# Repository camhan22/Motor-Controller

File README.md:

# Motor-Controller

12-48VDC 65A continuous (150A Peak) 0-100% duty cycle brushed DC motor driver 

Communicates to a master controller through I2C with commands that look like the following:

DSSSSSSS

Where D is the direction (0 or 1) (1 will apply +VDC to Motor+ Terminal) (0 Will apply +VDC to the Motor- Terminal)
S is the duty cycle from 0-100% (This is checked by the software to ensure it is within bounds) (Anything out of bounds is clamped to 100%)

I2C address can be changed with the dip switches on the board and allows up to 8 motor drivers to run at the same time.

Returns a status byte to describe what the controller is doing. If faults are present, there are seperate status codes for each failure and can be found within the code folder in the controller status codes excel sheet.

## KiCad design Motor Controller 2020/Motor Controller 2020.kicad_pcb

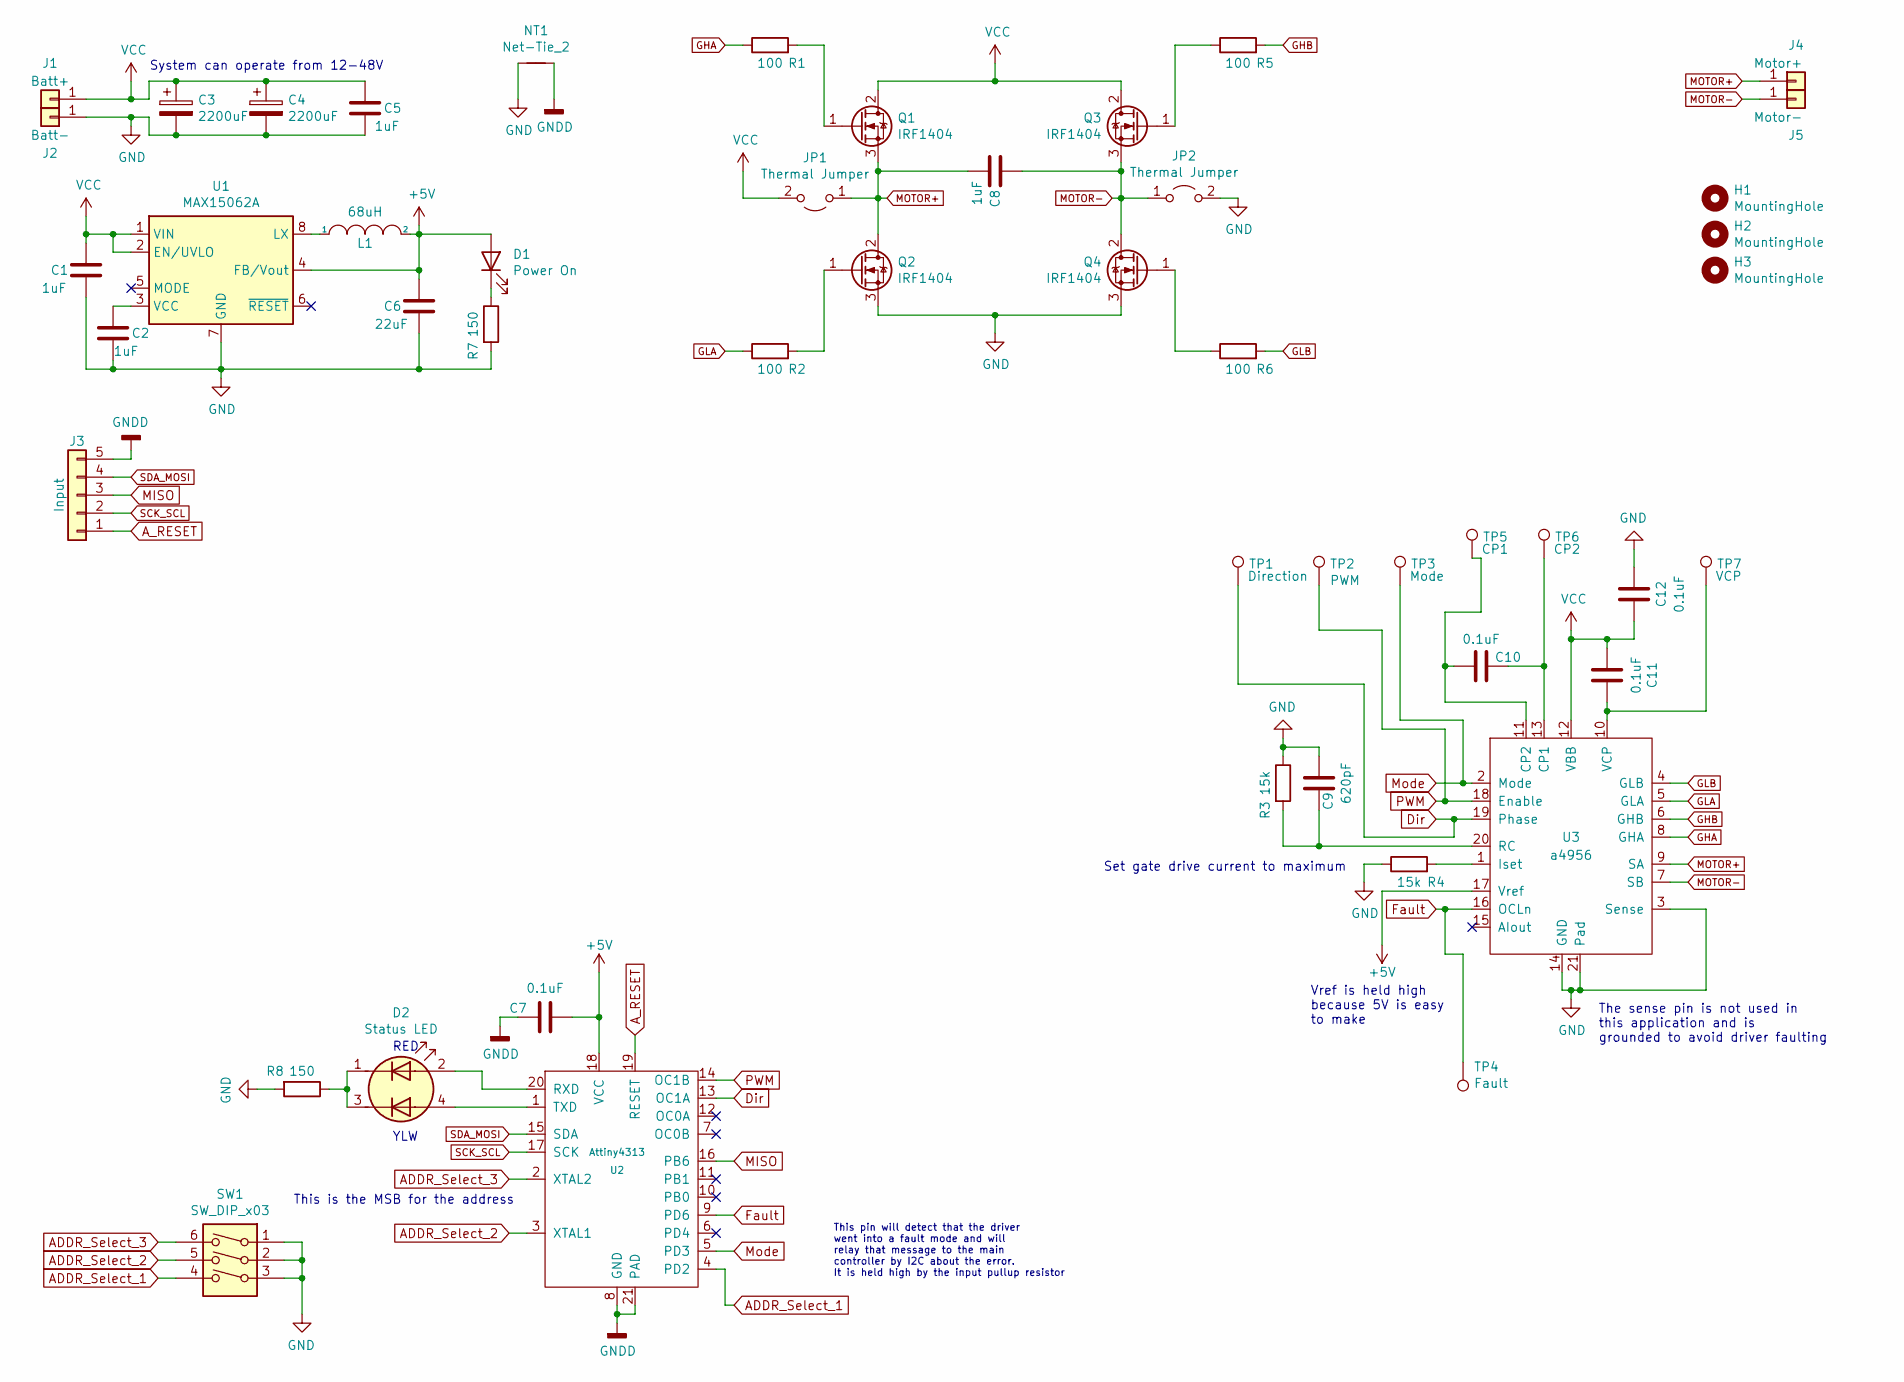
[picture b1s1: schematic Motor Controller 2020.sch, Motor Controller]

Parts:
C1, C2, C5: 1uF; C_1210_3225Metric
C3, C4: 2200uF; C_Radial_D18.0mm_H35.5mm_P7.50mm
C6: 22uF; C_1210_3225Metric
C7, C10, C11, C12: 0.1uF; C_1812_4532Metric_Pad1.57x3.40mm_HandSolder
C8: 1uF; C_Disc_D5.0mm_W2.5mm_P2.50mm
C9: 620pF; C_1210_3225Metric
D1: Power On; LED_1206_3216Metric
D2: Status LED; LED_0603_4_pin
H1, H2, H3: MountingHole; MountingHole_3.2mm_M3
J1: Batt+; Wuerth_REDCUBE-THR_WP-THRBU_74650195_THR
J2: Batt-; Wuerth_REDCUBE-THR_WP-THRBU_74650195_THR
J3: Input; Molex_KK-254_AE-6410-05A_1x05_P2.54mm_Vertical
J4: Motor+; Wuerth_REDCUBE-THR_WP-THRBU_74650195_THR
J5: Motor-; Wuerth_REDCUBE-THR_WP-THRBU_74650195_THR
JP1, JP2: Thermal Jumper; R_2512_6332Metric
L1: 68uH; L_1210_3225Metric
NT1: Net-Tie_2; NetTie-2_SMD_Pad2.0mm
Q1, Q2, Q3, Q4: IRF1404; TO-263-2
R1, R2, R5, R6: 100; R_2010_5025Metric
R3, R4: 15k; R_2010_5025Metric_Pad1.40x2.65mm_HandSolder
R7, R8: 150; R_1206_3216Metric
SW1: SW_DIP_x03; SW_DIP_SPSTx03_Slide_6.7x9.18mm_W8.61mm_P2.54mm_LowProfile
TP1: Direction; TestPoint_Pad_D1.0mm
TP2: PWM; TestPoint_Pad_D1.0mm
TP3: Mode; TestPoint_Pad_D1.0mm
TP4: Fault; TestPoint_Pad_D1.0mm
TP5: CP1; TestPoint_Pad_D1.0mm
TP6: CP2; TestPoint_Pad_D1.0mm
TP7: VCP; TestPoint_Pad_D1.0mm
U1: MAX15062A; DFN-8_2x2mm_P0.5mm
U2: Attiny4313; VQFN-20-1EP_3x3mm_P0.4mm_EP1.7x1.7mm_ThermalVias
U3: a4956; MLF-20-1EP_4x4mm_P0.5mm_EP2.6x2.6mm_ThermalVias

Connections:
+5V: C6.1, C7.2, D1.2 (A), L1.2, U1.4 (FB/Vout), U2.18 (VCC), U3.17 (Vref)
ADDR_Select_1: SW1.4, U2.4 (PD2)
ADDR_Select_2: SW1.5, U2.3 (XTAL1)
ADDR_Select_3: SW1.6, U2.2 (XTAL2)
A_RESET: J3.1, U2.19 (RESET)
Dir: TP1.1, U2.13 (OC1A), U3.19 (Phase)
Fault: TP4.1, U2.9 (PD6), U3.16 (OCLn)
GHA: R1.1, U3.8 (GHA)
GHB: R5.2, U3.6 (GHB)
GLA: R2.1, U3.5 (GLA)
GLB: R6.2, U3.4 (GLB)
GND: C1.2, C2.2, C3.2, C4.2, C5.2, C6.2, C9.2, C12.1, J2.1, JP2.2 (B), NT1.1, Q2.3 (S), Q4.3 (S), R3.1, R4.1, R7.2, R8.2, SW1.1, SW1.2, SW1.3, U1.7 (GND), U3.3 (Sense), U3.14 (GND), U3.21 (Pad)
GNDD: C7.1, J3.5, NT1.2, U2.8 (GND), U2.21 (PAD)
MISO: J3.3, U2.16 (PB6)
MOTOR+: C8.2, J4.1, JP1.1 (A), Q1.3 (S), Q2.2 (D), U3.9 (SA)
MOTOR-: C8.1, J5.1, JP2.1 (A), Q3.3 (S), Q4.2 (D), U3.7 (SB)
Mode: TP3.1, U2.5 (PD3), U3.2 (Mode)
unnamed: C2.1, U1.3 (VCC)
unnamed: C9.1, R3.2, U3.20 (RC)
unnamed: C10.1, TP6.1, U3.13 (CP1)
unnamed: C10.2, TP5.1, U3.11 (CP2)
unnamed: C11.2, TP7.1, U3.10 (VCP)
unnamed: D1.1 (K), R7.1
unnamed: D2.1 (A1), D2.3 (A2), R8.1
unnamed: D2.2 (K1), U2.20 (RXD)
unnamed: D2.4 (K2), U2.1 (TXD)
unnamed: L1.1, U1.8 (LX)
unnamed: Q1.1 (G), R1.2
unnamed: Q2.1 (G), R2.2
unnamed: Q3.1 (G), R5.1
unnamed: Q4.1 (G), R6.1
unnamed: R4.2, U3.1 (Iset)
PWM: TP2.1, U2.14 (OC1B), U3.18 (Enable)
SCK_SCL: J3.2, U2.17 (SCK)
SDA_MOSI: J3.4, U2.15 (SDA)
VCC: C1.1, C3.1, C4.1, C5.1, C11.1, C12.2, J1.1, JP1.2 (B), Q1.2 (D), Q3.2 (D), U1.1 (VIN), U1.2 (EN/UVLO), U3.12 (VBB)

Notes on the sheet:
This pin will detect that the driver went into a fault mode and will relay that message to the main controller by I2C about the error. It is held high by the input pullup resistor
This is the MSB for the address
The sense pin is not used in this application and is grounded to avoid driver faulting
Vref is held high because 5V is easy to make
Set gate drive current to maximum
System can operate from 12-48V
YLW
RED

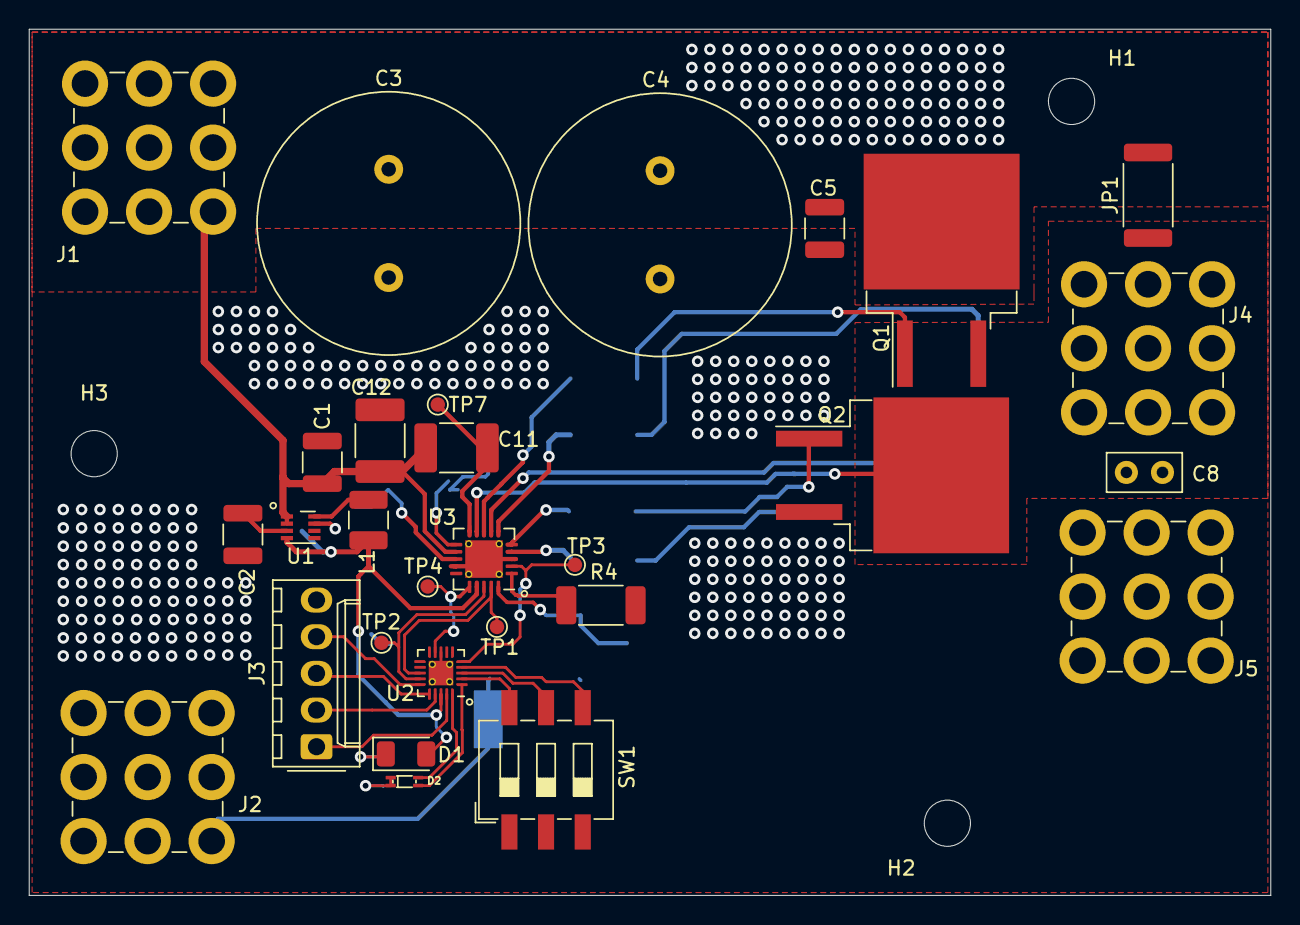
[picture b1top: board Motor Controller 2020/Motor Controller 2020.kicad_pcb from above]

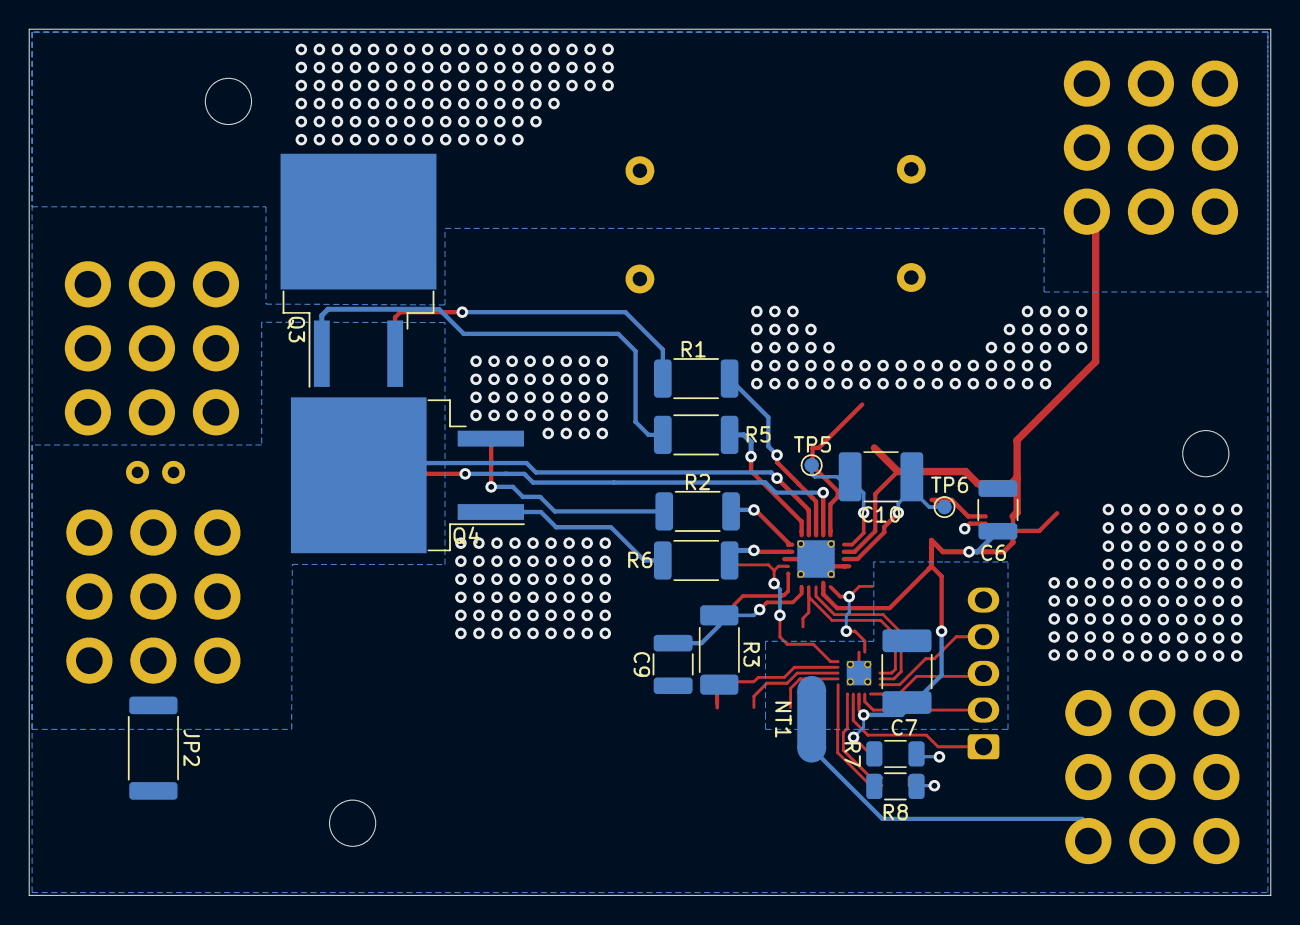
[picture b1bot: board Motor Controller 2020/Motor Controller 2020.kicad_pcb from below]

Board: 2 copper layers, 86.0 x 60.0 mm, 49 parts (17 on the bottom side), 36 nets.

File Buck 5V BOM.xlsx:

Schematic Annotation | Part Number | Description | Qty | Price | Supplier | Total Cost | Link
C7,C10,C11,C12 | 399-17501-1-ND | ±5% 50V Ceramic Capacitor X7R 1812 (4532 Metric) 0.1uF | 4 | 1.0900000000000001 | Digikey | 4.3600000000000003 | https://www.digikey.com/en/products/detail/kemet/C1812C104J5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
C8 | 445-173162-1-ND | 1 µF ±10% 100V Ceramic Capacitor X7R Radial | 1 | 0.73 | Digikey | 0.73 | https://www.digikey.com/en/products/detail/tdk-corporation/F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
C3,C4 | 1189-1505-ND | 2200 µF 63 V Aluminum Electrolytic Capacitors Radial, Can - 10000 Hrs @ 105°C | 2 | 2.92 | Digikey | 5.84 | https://www.digikey.com/en/products/detail/rubycon/63ZLH2200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
C9 | 478-10901-1-ND | CAP CER 620PF 100V NP0 1210 | 1 | 0.49 | Digikey | 0.49 | https://www.digikey.com/en/products/detail/avx-corporation/1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
R3,R4 | 541-15.0KACCT-ND | 15 kOhms ±1% 0.75W, 3/4W Chip Resistor 2010 (5025 Metric) Automotive AEC-Q200 T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 | 2 | 0.3 | Digikey | 0.6 | https://www.digikey.com/en/products/detail/vishay-dale/CRCW2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
D1 | 1080-1419-1-ND | Green 570nm LED Indication - Discrete 2.1V 1206 (3216 Metric) | 1 | 0.37 | Digikey | 0.37 | https://www.digikey.com/en/products/detail/QTLP650D4TR/1080-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
D2 | 1516-QBLP601-RYCT-ND | Red, Yellow 630nm Red, 591nm Yellow LED Indication - Discrete 2V Red, 2V Yellow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 | 1 | 0.43 | Digikey | 0.43 | https://www.digikey.com/en/products/detail/qt-brightek-qtb/Q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
R7,R8 | 311-150LJCT-ND | 150 Ohms ±1% 0.25W, 1/4W Chip Resistor 1206 (3216 Metric) Automotive AEC-Q200, 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 | 2 | 0.1 | Digikey | 0.2 | https://www.digikey.com/en/products/detail/AC1206FR-07150RL/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
Q1-Q4 | IRFS3306TRLPBFCT-ND | N-Channel 60 V 120A (Tc) 230W (Tc) Surface Mount D2PAK | 4 | 2.58 | Digikey | 10.32 | https://www.infineon.com/dgdl/irfs3306pbf.pdf?fileId=5546d46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
U3 | 620-1772-1-ND | Motor Driver NMOS Parallel | 1 | 1.64 | Digikey | 1.64 | https://www.digikey.com/en/products/detail/allegro-microsyst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
U1 | 175-MAX17640BATA+-ND | Buck Switching Regulator IC Positive Fixed 5V 1 Output 400mA 8-WFDFN | 1 | 1.65 | Digikey | 1.65 | https://www.digikey.com/en/products/detail/maxim-integrated/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
L1 | 587-3070-1-ND | 68 µH Unshielded Wirewound Inductor 410 mA 1.3Ohm Max 1210 (3225 Metric) | 1 | 0.3 | Digikey | 0.3 | https://www.digikey.com/en/products/detail/CBC3225T680KR/587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
C6 | 1276-CL32B226MOJVPNECT-ND | 22 µF ±20% 16V Ceramic Capacitor X7R 1210 (3225 Metric) | 1 | 0.71 | Digikey | 0.71 | CL32B226MOJVPNE Samsung Electro-Mechanics | Capacitors | DigiKey
C1,C2,C5 | 2873-C1210X105K101TCT-ND | 1 µF ±10% 100V Ceramic Capacitor X7R 1210 (3225 Metric) | 4 | 0.35 | Digikey | 1.4 | https://www.digikey.com/en/products/detail/holy-stone-enterp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
J1,J2,J4,J5 | 732-10888-1-ND | Pin Screw Terminal, Power Tap M5 Through Hole | 4 | 4.59 | Digikey | 18.36 | https://www.digikey.com/en/products/detail/w%C3%BCrth-elektr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
J3 | 23-0022292051-ND | Connector Header Through Hole 5 position 0.100" (2.54mm) | 1 | 1.43 | Digikey | 1.43 | https://www.digikey.com/en/products/detail/molex/0022292051/1130591
J3 Conn | 23-0010112053-ND | 5 Rectangular Connectors - Housings Receptacle White 0.100" (2.54mm) | 1 | 0.28999999999999998 | Digikey | 0.28999999999999998 | https://www.digikey.com/en/products/detail/molex/0010112053/171981
J3 Crimp | WM23941CT-ND | Non-Gendered Contact Gold 24-30 AWG Crimp - | 9 | 0.39 | Digikey | 3.5100000000000002 | https://www.digikey.com/en/products/detail/molex/0008550124/1784904
SW1 | 2223-DS04-254-2-03BK-SMT-ND | Dip Switch SPST Position Surface Mount Slide (Standard) Actuator 25mA 24VDC | 1 | 0.54 | Digikey | 0.54 | https://www.digikey.com/en/products/detail/cui-devices/DS04-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
JP1,JP2 | 764-THJP2512AST1CT-ND | Thermal Interface Products Therm Jumper 30 mil 2512 | 2 | 1.35 | Digikey | 2.7 | https://www.digikey.com/en/products/detail/vishay-dale-thin-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
 | 277-11158-ND | Ring Terminal Connector M5 Stud Circular 10-14 AWG Crimp | 4 | 0.26 | Digikey | 1.04 | https://www.digikey.com/en/products/detail/phoenix-contact/3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
R1,R2,R5,R6 | RMCP2010JT100RCT-ND | 100 Ohms ±5% 1W Chip Resistor 2010 (5025 Metric) Automotive AEC-Q200 Thick Film | 4 | 0.41 | Digikey | 1.64 | https://www.digikey.com/en/products/detail/stackpole-electro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
U2 | ATTINY4313-MMHRCT-ND | 8-bit Microcontrollers - MCU AVR 4KB FL 256B SRAM 256B 20MHz 1.8-5.5V | 1 | 0.97 | Digikey | 0.97 | https://www.digikey.com/en/products/detail/microchip-technol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
 |  |  |  |  | Total Cost | 59.519999999999989

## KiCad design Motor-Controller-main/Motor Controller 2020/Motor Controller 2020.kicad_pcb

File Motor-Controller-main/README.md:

# Motor-Controller
12V Brushed DC motor controller made for FIRST robotics CIM motor

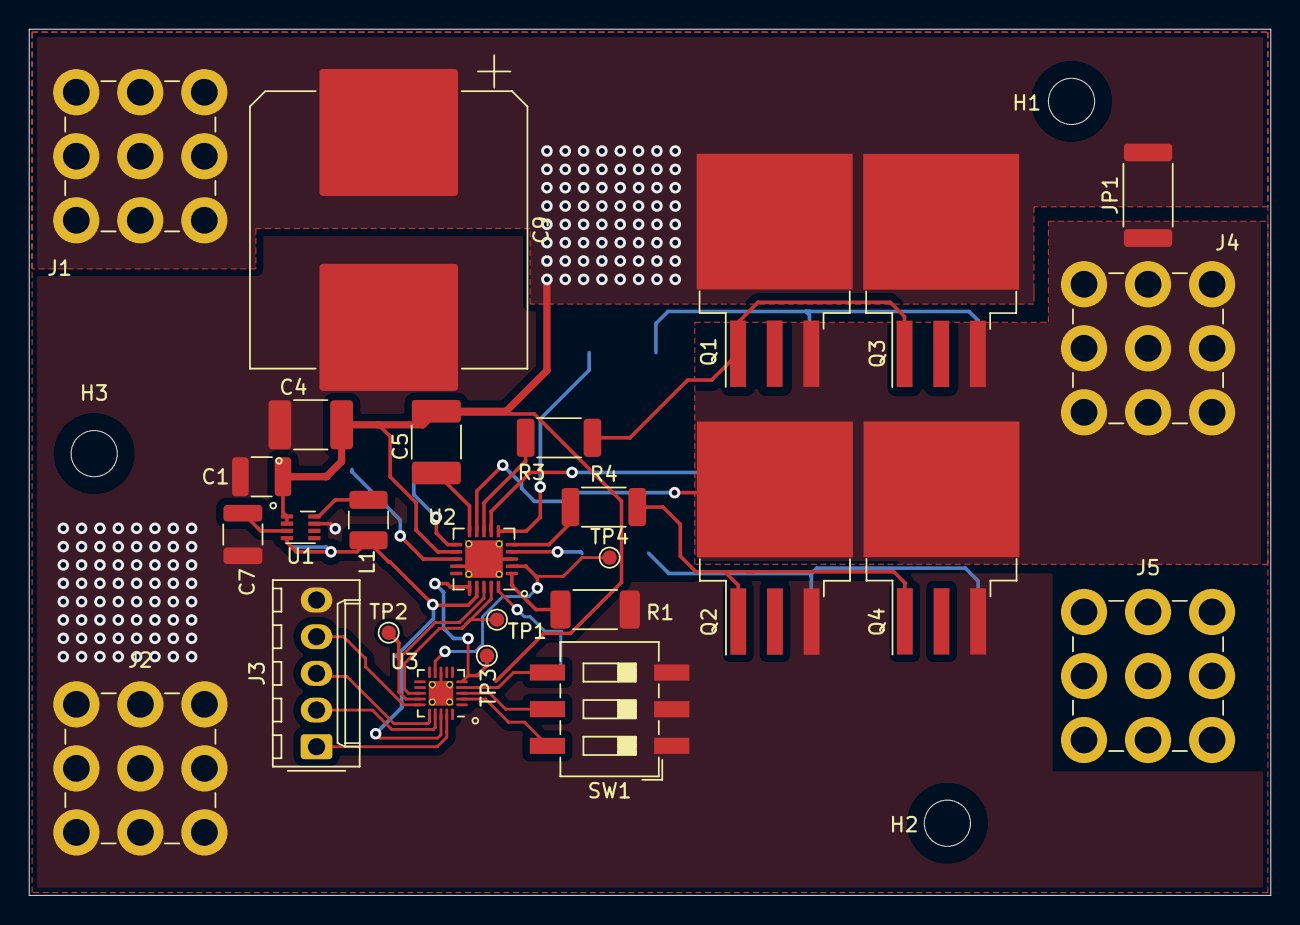
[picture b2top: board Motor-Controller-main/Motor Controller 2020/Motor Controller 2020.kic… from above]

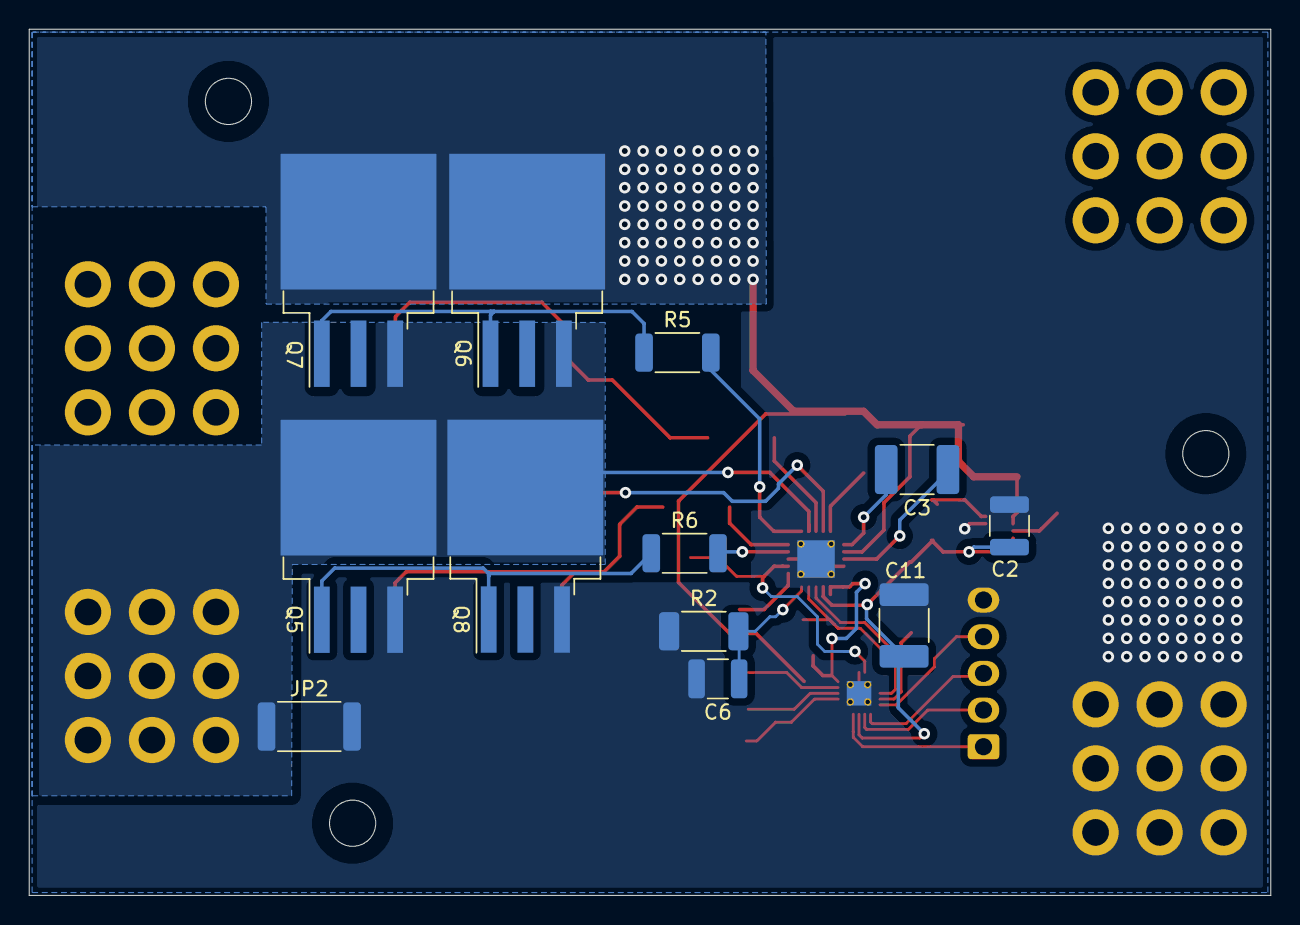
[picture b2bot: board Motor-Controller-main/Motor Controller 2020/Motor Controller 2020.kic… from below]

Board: 2 copper layers, 86.0 x 60.0 mm, 42 parts (12 on the bottom side), 31 nets.

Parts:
C1, C7: 1uF; C_1210_3225Metric
C2: 10uF; C_1210_3225Metric
C3, C4, C11: 0.1uF; C_1812_4532Metric_Pad1.57x3.40mm_HandSolder
C5: 0.47uF; C_1812_4532Metric_Pad1.57x3.40mm_HandSolder
C6: 620pF; C_1210_3225Metric
C9: 4700uF; CP_Elec_18x17.5
H1, H2, H3: MountingHole; MountingHole_3.2mm_M3
J1: Batt+; Wuerth_REDCUBE-THR_WP-THRBU_74650195_THR
J2: Batt-; Wuerth_REDCUBE-THR_WP-THRBU_74650195_THR
J3: Input; Molex_KK-254_AE-6410-05A_1x05_P2.54mm_Vertical
J4: Motor+; Wuerth_REDCUBE-THR_WP-THRBU_74650195_THR
J5: Motor-; Wuerth_REDCUBE-THR_WP-THRBU_74650195_THR
JP1, JP2: Thermal Jumper; R_2512_6332Metric
L1: 47uH; L_1210_3225Metric
Q1, Q2, Q3, Q4, Q5, Q6, Q7, Q8: IRF1404; TO-263-3_TabPin2
R1, R2: 15k; R_2010_5025Metric_Pad1.40x2.65mm_HandSolder
R3, R4, R5, R6: 100; R_2010_5025Metric
SW1: SW_DIP_x03; SW_DIP_SPSTx03_Slide_6.7x9.18mm_W8.61mm_P2.54mm_LowProfile
TP1, TP2, TP3, TP4: TestPoint; TestPoint_Pad_D1.0mm
U1: MAX15062A; DFN-8_2x2mm_P0.5mm
U2: a4956; MLF-20-1EP_4x4mm_P0.5mm_EP2.6x2.6mm_ThermalVias
U3: Attiny4313; VQFN-20-1EP_3x3mm_P0.4mm_EP1.7x1.7mm_ThermalVias

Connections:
+5V: C2.1, C11.2, L1.2, U1.4, U2.17, U3.18
+12V: C1.1, C4.2, C5.1, C9.1, J1.1, JP1.2, Q1.2, Q3.2, Q6.2, Q7.2, U1.1, U1.2, U2.12
ADDR_Select_1: SW1.4, U3.4
ADDR_Select_2: SW1.5, U3.3
ADDR_Select_3: SW1.6, U3.2
A_RESET: J3.1, U3.19
Dir: TP1.1, U2.19, U3.13
Fault: TP3.1, U2.16, U3.5
GHA: R3.1, U2.8
GHB: R5.2, U2.6
GLA: R4.1, U2.5
GLB: R6.2, U2.4
GND: C1.2, C2.2, C4.1, C6.2, C7.2, C9.2, C11.1, J2.1, J3.5, JP2.2, Q2.3, Q4.3, Q5.3, Q8.3, R1.1, R2.1, SW1.1, SW1.2, SW1.3, U1.7, U2.3, U2.14, U2.21, U3.8, U3.21
MISO: J3.3, U3.16
MOTOR+: J4.1, JP1.1, Q1.3, Q2.2, Q3.3, Q4.2, U2.9
MOTOR-: J5.1, JP2.1, Q5.2, Q6.3, Q7.3, Q8.2, U2.7
Mode: TP4.1, U2.2, U3.9
unnamed: C3.1, U2.13
unnamed: C3.2, U2.11
unnamed: C5.2, U2.10
unnamed: C6.1, R2.2, U2.20
unnamed: C7.1, U1.3
unnamed: L1.1, U1.8
unnamed: Q1.1, Q3.1, R3.2
unnamed: Q2.1, Q4.1, R4.2
unnamed: Q5.1, Q8.1, R6.1
unnamed: Q6.1, Q7.1, R5.1
unnamed: R1.2, U2.1
PWM: TP2.1, U2.18, U3.14
SCK_SCL: J3.2, U3.17
SDA_MOSI: J3.4, U3.15

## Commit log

2021-06-15 Added existing files
2021-06-17 Added reset/program jumper to board
2021-06-17 Added mounting holes instead of trying to slide the board into the housing
    The 3D printed slide mechanism didn't work because the printer couldn't reproduce the sharp corners
2021-06-18 Added Step file for controller
2021-06-20 Bug fixes and code readability changes
2021-06-22 Fixed driver reset bugs
2021-06-22 Tested Reset Code
2021-06-23 Fixed Startup issues
2021-06-30 Updated PCB to DC-DC Converter
    Also changed associated BOM lines. Created a notes document to show what it can do.
2021-06-30 Added STL files for case
2021-06-30 Added motor modeling
2021-07-01 Updated controller PCB
    Added several capacitors to help with switching transients
2021-07-02 Updated Controller board
    Separated the logic and power GNDs to minimize noise. Added more Vias for current capability. Rerouted MOSFET tracks to be nearly the same length. Filleted the corners on copper pours. Added more tes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
2021-07-02 Updated schematic and PCB
    Reduced the loop length to just over half the original length. Added more Vias for stitching. Changed MOSFET to handle up to 48V, meaning that the system can work up to 48V while still maintaining th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
2021-07-06 Re-arranged components
2021-07-07 Updated PCB
    Added larger caps for local storage. Also removed 4 MOSFETS because I don't believe I will need them. This will be tested when the system works properly
2021-07-13 Remade and checked gerber files
2021-07-22 Made gerber files
2021-08-06 Added status lights
    Added power and status lights to help diagnose issues when the system is running without screen on the master controller
2021-08-14 Updated Code
2021-08-15 Updated CAD Model
2021-08-20 Housekeeping
    Added datasheets and changed readme
2021-08-20 Added this to readme
2021-08-20 Moved to references folder
2021-09-07 Updated Parts to match what was bought
2021-10-11 created stl files
2021-10-19 Updated code and BOM
    Added code to check for a CRC to ensure data is correct.
    Also changed the BOM to allow for a shorter controller design
2021-10-26 Created new version
    Updated PCB and added CRC check for incoming data
2022-01-14 Updated PCB
